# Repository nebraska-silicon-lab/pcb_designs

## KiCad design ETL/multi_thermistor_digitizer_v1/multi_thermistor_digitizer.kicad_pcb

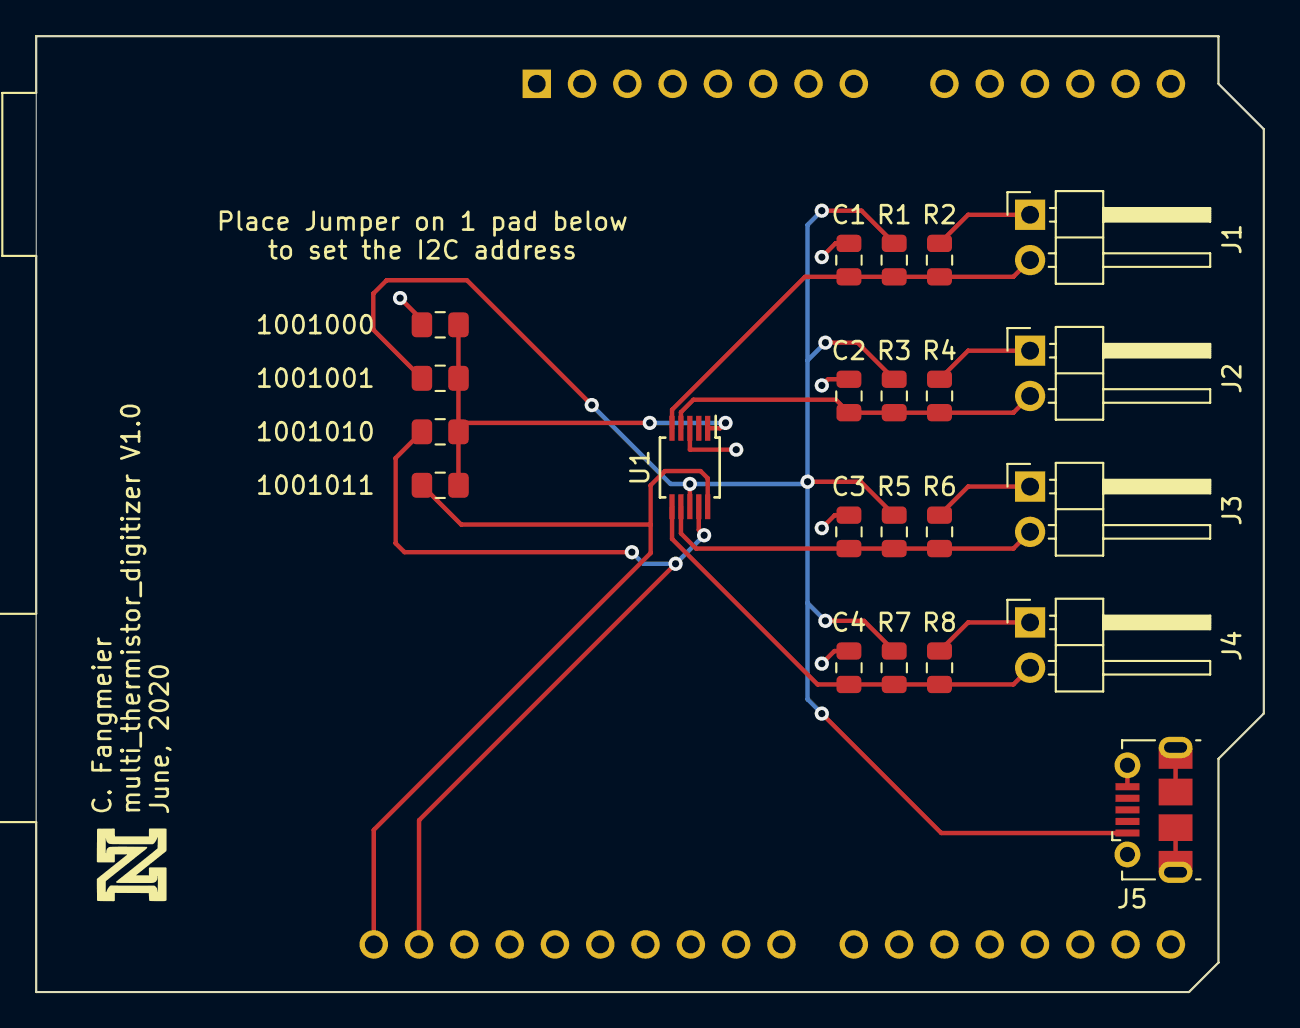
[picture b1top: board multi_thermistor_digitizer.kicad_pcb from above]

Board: 2 copper layers, 68.8 x 53.6 mm, 23 parts (0 on the bottom side), 9 nets.

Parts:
A1: Arduino_UNO_R3
C1, C2, C3, C4: 10uF; C_0805_2012Metric
J1, J2, J3, J4: Conn_01x02; PinHeader_1x02_P2.54mm_Horizontal
J5: USB_B_Micro; USB_Micro-B_Molex-105017-0001
JP1, JP2, JP3, JP4: Jumper_NO_Small; R_0805_2012Metric_Pad1.15x1.40mm_HandSolder
R1, R2, R3, R4, R5, R6, R7, R8: 5k; C_0805_2012Metric
U1: ADS1115IDGS; MSOP-10_3x3mm_P0.5mm

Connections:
/5V: J5.1, JP2.2, R1.2, R3.2, R5.2, R7.2, U1.8
/SCL: A1.32, JP4.2, U1.10
/SDA: A1.31, JP3.2, U1.9
/Vsense0: C1.1, J1.2, R1.1, R2.1, U1.5
/Vsense1: C2.1, J2.2, R3.1, R4.1, U1.4
/Vsense2: C3.1, J3.2, R5.1, R6.1, U1.7
/Vsense3: C4.1, J4.2, R7.1, R8.1, U1.6
GND: A1.6, A1.7, A1.29, C1.2, C2.2, C3.2, C4.2, J1.1, J2.1, J3.1, J4.1, J5.5, J5.6, JP1.2, R2.2, R4.2, R6.2, R8.2, U1.3
unnamed: JP1.1, JP2.1, JP3.1, JP4.1, U1.1

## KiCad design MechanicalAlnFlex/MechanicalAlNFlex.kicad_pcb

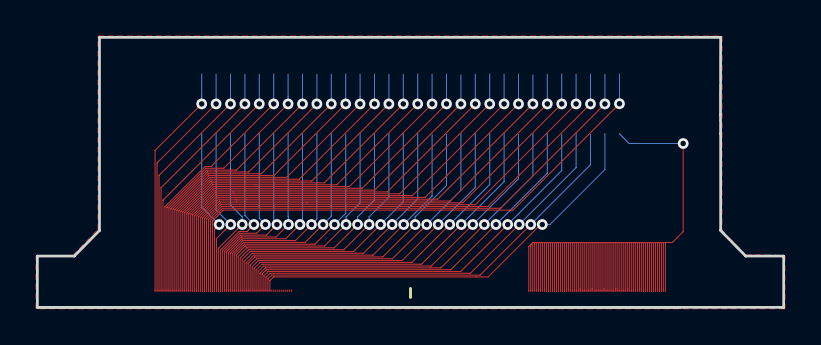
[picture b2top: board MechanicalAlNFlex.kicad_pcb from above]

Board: 2 copper layers, 41.5 x 15.0 mm, 3 parts (0 on the bottom side), 60 nets.

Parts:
J1: Conn_02x30_Odd_Even; SAMTEC_FTE-130-01-G-DV-EC
J2, J3: Conn_02x35_Top_Bottom; ETROC_70pad_61x126um_110um_pitch

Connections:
/COM: J1.1, J3.1, J3.2, J3.3, J3.4, J3.5, J3.6, J3.7, J3.8, J3.9, J3.10, J3.11, J3.12, J3.13, J3.14, J3.15, J3.16, J3.17, J3.18, J3.19, J3.20, J3.21, J3.22, J3.23, J3.24, J3.25, J3.26, J3.27, J3.28, J3.29, J3.30, J3.31, J3.32, J3.33, J3.34, J3.35, J3.36, J3.37, J3.38, J3.39, J3.40, J3.41, J3.42, J3.43, J3.44, J3.45, J3.46, J3.47, J3.48, J3.49, J3.50, J3.51, J3.52, J3.53, J3.54, J3.55, J3.56, J3.57, J3.58, J3.59, J3.60, J3.61, J3.62, J3.63, J3.64, J3.65, J3.66, J3.67, J3.68, J3.69, J3.70
/P1: J1.60, J2.1
/P2: J1.58, J2.2
/P3: J1.56, J2.3
/P4: J1.54, J2.4
/P5: J1.52, J2.5
/P6: J1.50, J2.6
/P7: J1.48, J2.7
/P8: J1.46, J2.8
/P9: J1.44, J2.9
/P10: J1.42, J2.10
/P11: J1.40, J2.11
/P12: J1.38, J2.12
/P13: J1.36, J2.13
/P14: J1.34, J2.14
/P15: J1.32, J2.15
/P16: J1.30, J2.16
/P17: J1.28, J2.17
/P18: J1.26, J2.18
/P19: J1.24, J2.19
/P20: J1.22, J2.20
/P21: J1.20, J2.21
/P22: J1.18, J2.22
/P23: J1.16, J2.23
/P24: J1.14, J2.24
/P25: J1.12, J2.25
/P26: J1.10, J2.26
/P27: J1.8, J2.27
/P28: J1.6, J2.28
/P29: J1.4, J2.29
/P30: J1.2, J2.30
/P31: J1.59, J2.31
/P32: J1.57, J2.32
/P33: J1.55, J2.33
/P34: J1.53, J2.34
/P35: J1.51, J2.35
/P36: J1.49, J2.36
/P37: J1.47, J2.37
/P38: J1.45, J2.38
/P39: J1.43, J2.39
/P40: J1.41, J2.40
/P41: J1.39, J2.41
/P42: J1.37, J2.42
/P43: J1.35, J2.43
/P44: J1.33, J2.44
/P45: J1.31, J2.45
/P46: J1.29, J2.46
/P47: J1.27, J2.47
/P48: J1.25, J2.48
/P49: J1.23, J2.49
/P50: J1.21, J2.50
/P51: J1.19, J2.51
/P52: J1.17, J2.52
/P53: J1.15, J2.53
/P54: J1.13, J2.54
/P55: J1.11, J2.55
/P56: J1.9, J2.56
/P57: J1.7, J2.57
/P58: J1.5, J2.58
/P59: J1.3, J2.59
